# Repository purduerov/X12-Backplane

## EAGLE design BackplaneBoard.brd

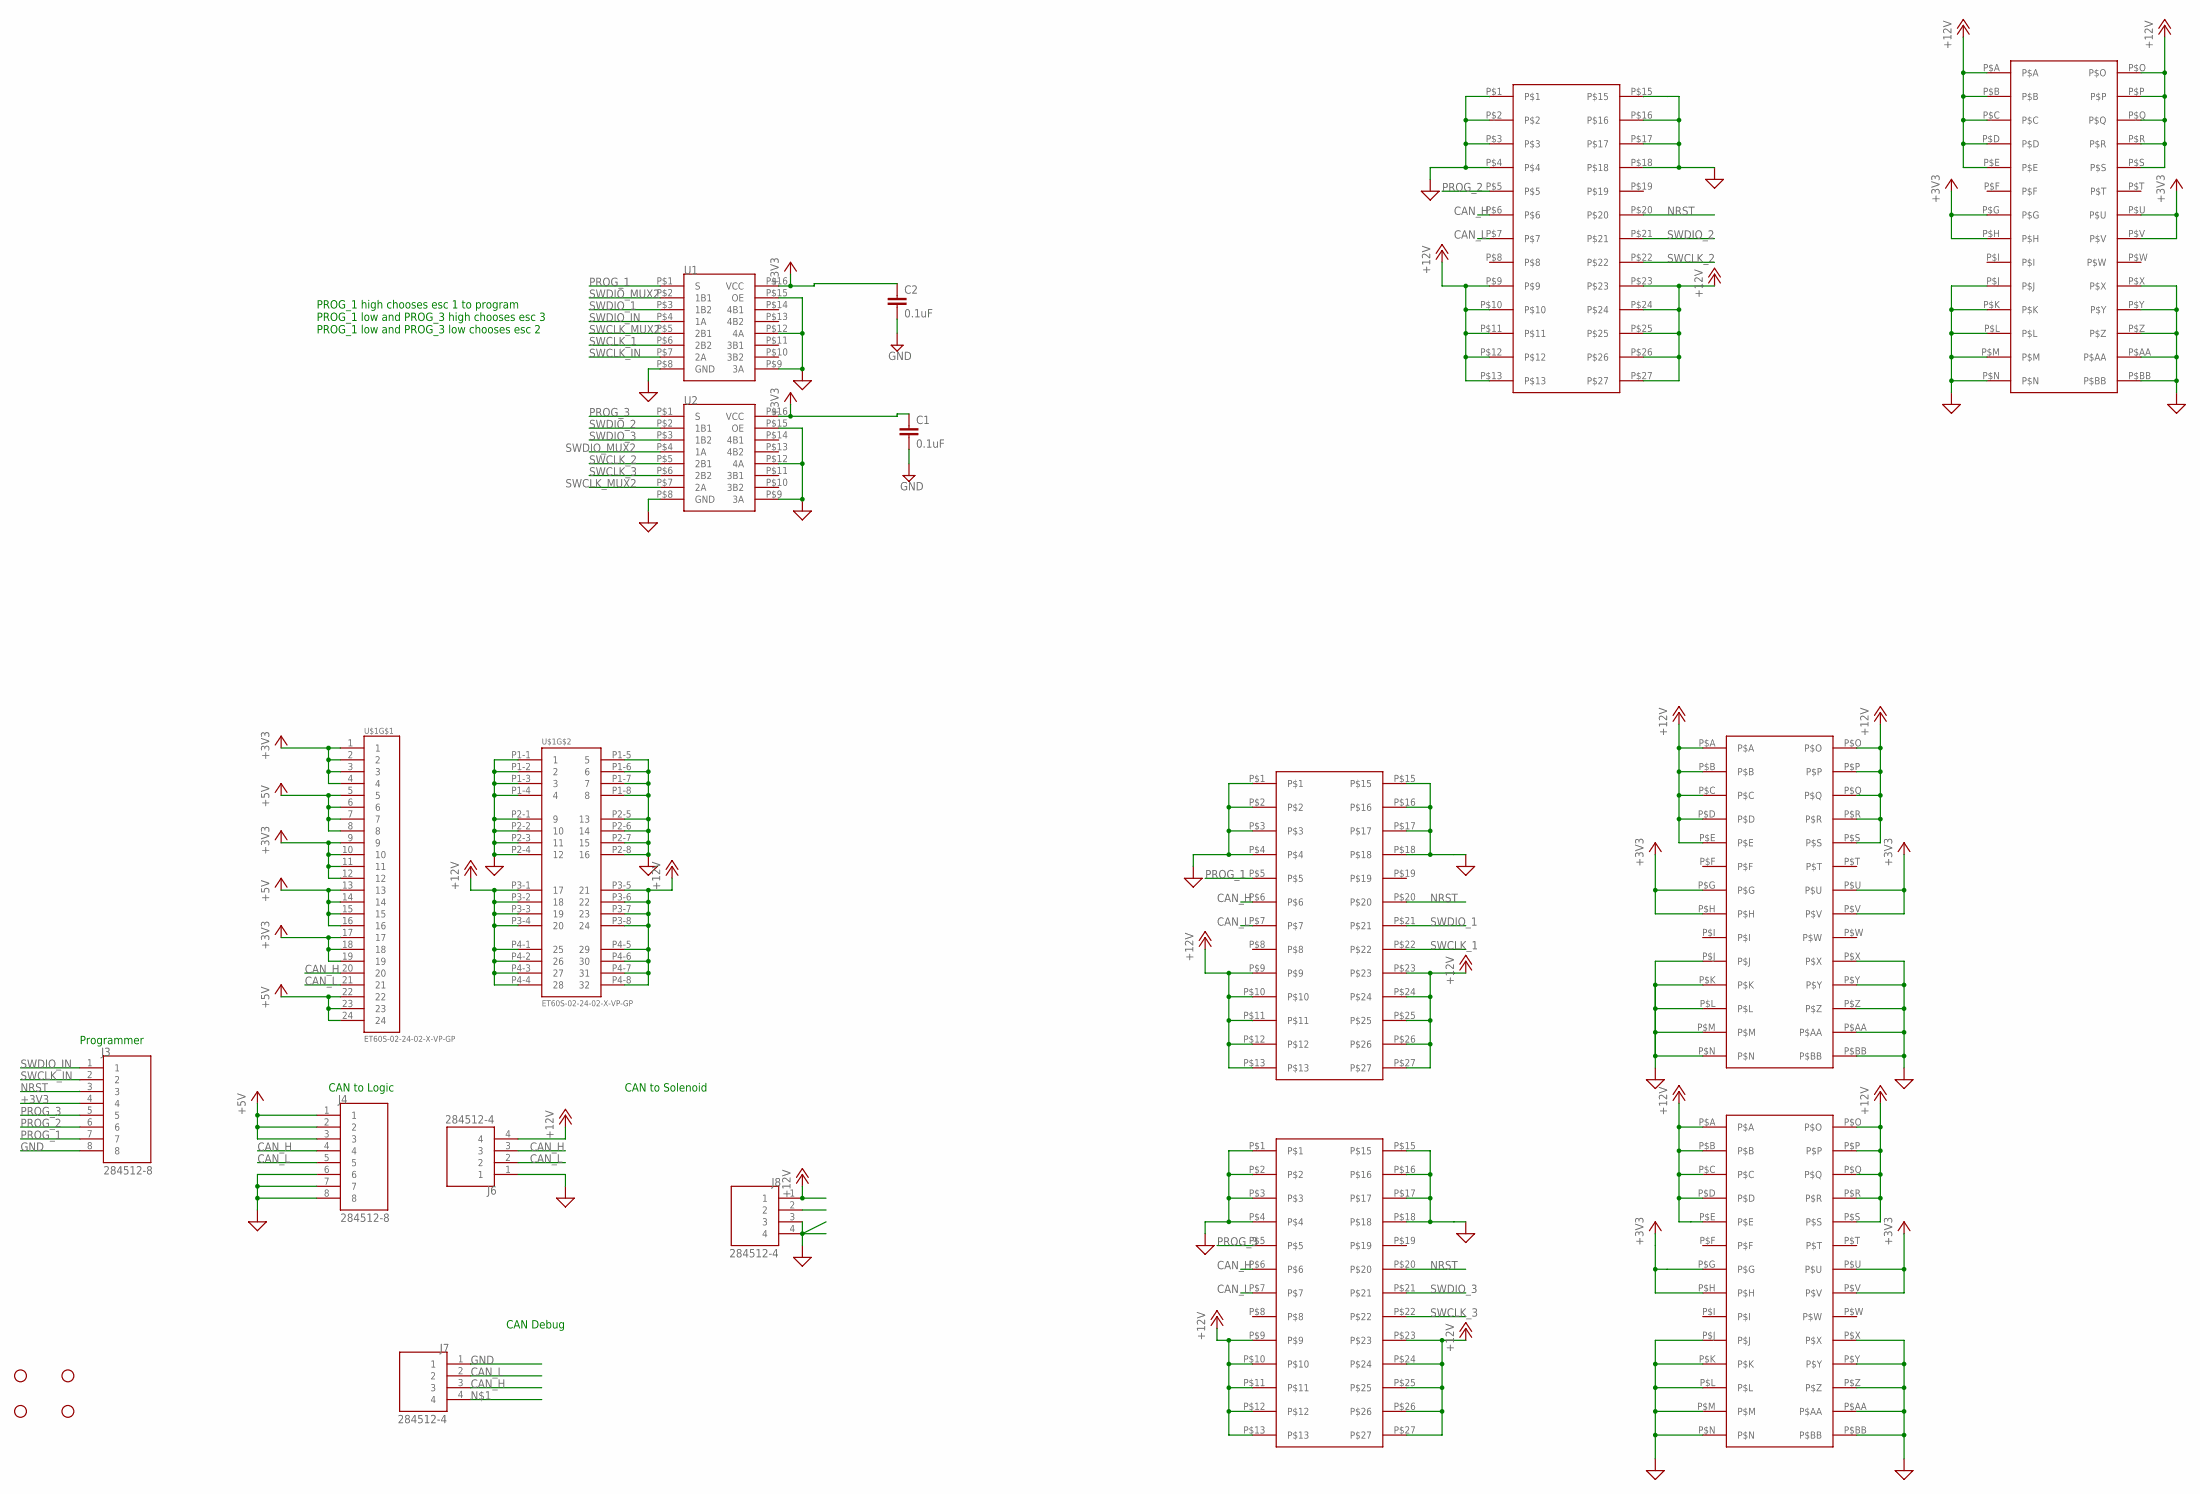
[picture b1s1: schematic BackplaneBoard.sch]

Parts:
C1, C2: 0.1uF; 0603
H1, H2, H3, H4: STAND-OFF
J3, J4: 284512-8; TE_284512-8
J6, J7, J8: 284512-4; TE_284512-4
U1, U2: SN74CBTLV3257PWR
U$1: ET60S-02-24-02-X-VP-GP
U$2, U$3, U$4: ESC2BACKPLANE; ESC2BACKPLANE_WHOLE

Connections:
+3V3: C1.1, C2.1, J3.4, U1.P$16 (VCC), U2.P$16 (VCC), U$1.1, U$1.2, U$1.3, U$1.4, U$1.9, U$1.10, U$1.11, U$1.12, U$1.17, U$1.18, U$1.19, U$2.P$G, U$2.P$H, U$2.P$U, U$2.P$V, U$3.P$G, U$3.P$H, U$3.P$U, U$3.P$V, U$4.P$G, U$4.P$H, U$4.P$U, U$4.P$V
+5V: J4.1, J4.2, J4.3, U$1.5, U$1.6, U$1.7, U$1.8, U$1.13, U$1.14, U$1.15, U$1.16, U$1.22, U$1.23, U$1.24
+12V: J6.4, J8.1, J8.2, U$1.P3-1 (17), U$1.P3-2 (18), U$1.P3-3 (19), U$1.P3-4 (20), U$1.P3-5 (21), U$1.P3-6 (22), U$1.P3-7 (23), U$1.P3-8 (24), U$1.P4-1 (25), U$1.P4-2 (26), U$1.P4-3 (27), U$1.P4-4 (28), U$1.P4-5 (29), U$1.P4-6 (30), U$1.P4-7 (31), U$1.P4-8 (32), U$2.P$9, U$2.P$10, U$2.P$11, U$2.P$12, U$2.P$13, U$2.P$23, U$2.P$24, U$2.P$25, U$2.P$26, U$2.P$27, U$2.P$A, U$2.P$B, U$2.P$C, U$2.P$D, U$2.P$E, U$2.P$O, U$2.P$P, U$2.P$Q, U$2.P$R, U$2.P$S, U$3.P$9, U$3.P$10, U$3.P$11, U$3.P$12, U$3.P$13, U$3.P$23, U$3.P$24, U$3.P$25, U$3.P$26, U$3.P$27, U$3.P$A, U$3.P$B, U$3.P$C, U$3.P$D, U$3.P$E, U$3.P$O, U$3.P$P, U$3.P$Q, U$3.P$R, U$3.P$S, U$4.P$9, U$4.P$10, U$4.P$11, U$4.P$12, U$4.P$13, U$4.P$23, U$4.P$24, U$4.P$25, U$4.P$26, U$4.P$27, U$4.P$A, U$4.P$B, U$4.P$C, U$4.P$D, U$4.P$E, U$4.P$O, U$4.P$P, U$4.P$Q, U$4.P$R, U$4.P$S
CAN_H: J4.4, J6.3, J7.3, U$1.20, U$2.P$6, U$3.P$6, U$4.P$6
CAN_L: J4.5, J6.2, J7.2, U$1.21, U$2.P$7, U$3.P$7, U$4.P$7
GND: C1.2, C2.2, J3.8, J4.6, J4.7, J4.8, J6.1, J7.1, J8.3, J8.4, U1.P$8 (GND), U1.P$9 (3A), U1.P$12 (4A), U1.P$15 (OE), U2.P$8 (GND), U2.P$9 (3A), U2.P$12 (4A), U2.P$15 (OE), U$1.P1-1 (1), U$1.P1-2 (2), U$1.P1-3 (3), U$1.P1-4 (4), U$1.P1-5 (5), U$1.P1-6 (6), U$1.P1-7 (7), U$1.P1-8 (8), U$1.P2-1 (9), U$1.P2-2 (10), U$1.P2-3 (11), U$1.P2-4 (12), U$1.P2-5 (13), U$1.P2-6 (14), U$1.P2-7 (15), U$1.P2-8 (16), U$2.P$1, U$2.P$2, U$2.P$3, U$2.P$4, U$2.P$15, U$2.P$16, U$2.P$17, U$2.P$18, U$2.P$AA, U$2.P$BB, U$2.P$J, U$2.P$K, U$2.P$L, U$2.P$M, U$2.P$N, U$2.P$X, U$2.P$Y, U$2.P$Z, U$3.P$1, U$3.P$2, U$3.P$3, U$3.P$4, U$3.P$15, U$3.P$16, U$3.P$17, U$3.P$18, U$3.P$AA, U$3.P$BB, U$3.P$J, U$3.P$K, U$3.P$L, U$3.P$M, U$3.P$N, U$3.P$X, U$3.P$Y, U$3.P$Z, U$4.P$1, U$4.P$2, U$4.P$3, U$4.P$4, U$4.P$15, U$4.P$16, U$4.P$17, U$4.P$18, U$4.P$AA, U$4.P$BB, U$4.P$J, U$4.P$K, U$4.P$L, U$4.P$M, U$4.P$N, U$4.P$X, U$4.P$Y, U$4.P$Z
NRST: J3.3, U$2.P$20, U$3.P$20, U$4.P$20
PROG_1: J3.7, U1.P$1 (S), U$2.P$5
PROG_2: J3.6, U$3.P$5
PROG_3: J3.5, U2.P$1 (S), U$4.P$5
SWCLK_1: U1.P$6 (2B2), U$2.P$22
SWCLK_2: U2.P$5 (2B1), U$3.P$22
SWCLK_3: U2.P$6 (2B2), U$4.P$22
SWCLK_IN: J3.2, U1.P$7 (2A)
SWCLK_MUX2: U1.P$5 (2B1), U2.P$7 (2A)
SWDIO_1: U1.P$3 (1B2), U$2.P$21
SWDIO_2: U2.P$2 (1B1), U$3.P$21
SWDIO_3: U2.P$3 (1B2), U$4.P$21
SWDIO_IN: J3.1, U1.P$4 (1A)
SWDIO_MUX2: U1.P$2 (1B1), U2.P$4 (1A)

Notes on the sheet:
CAN to Logic
CAN to Solenoid
Programmer
PROG_1 high chooses esc 1 to program PROG_1 low and PROG_3 high chooses esc 3 PROG_1 low and PROG_3 low chooses esc 2
CAN Debug

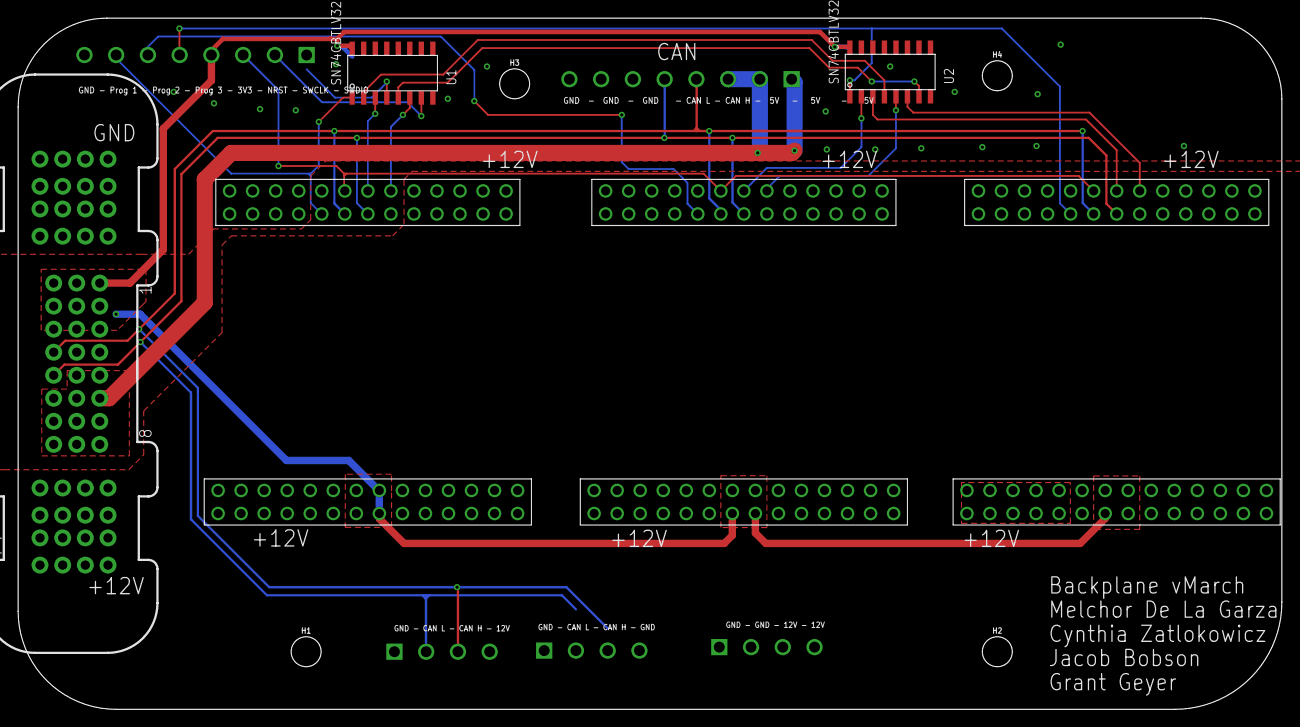
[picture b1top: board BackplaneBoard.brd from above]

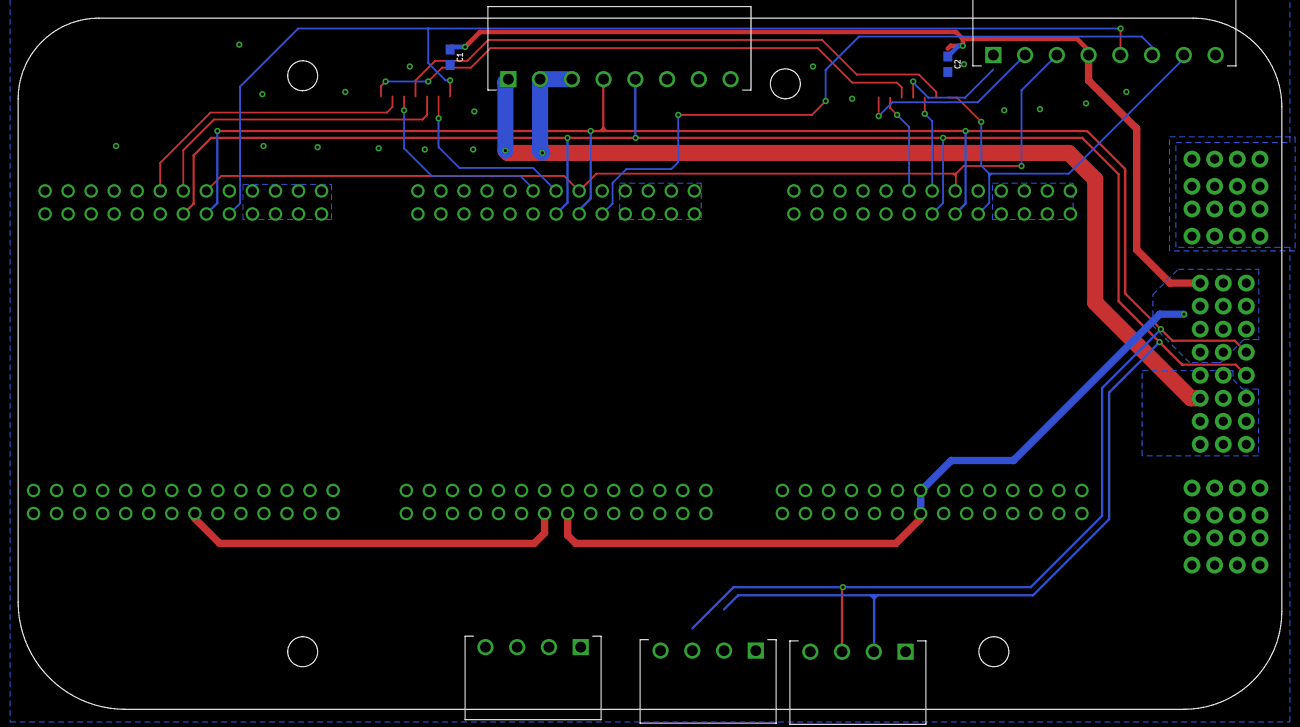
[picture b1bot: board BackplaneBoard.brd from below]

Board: 2 copper layers, 139.3 x 76.2 mm, 17 parts (7 on the bottom side), 20 nets.

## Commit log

2019-09-21 Send it off
2019-10-02 test
2019-11-03 Added right connectors to board
    added right connectors and put board size in, Melchor is slacking
2019-11-04 updated connectors
2019-11-04 added connectors
2019-11-05 updated connectors to jacobs liking
2019-11-05 moved some connectors
2019-11-05 added holes for standoffs
2019-11-07 Netted and labeled pins
2019-11-08 Added polygons to each signal coming from the ESC connecot pins to see placement and corrected a mistake on netting pins
2019-11-09 Added more connections to the pins
    something something did something
2019-11-13 Version1 of the backplane board
2019-11-13 Made Some adjustments
2019-11-15 V2 of Backplane
2019-11-15 fixeey
2019-11-18 Version #3
2019-11-21 Version 4
2019-12-16 edited GND plane
2019-12-16 Small routing changes
2019-12-19 Final Board
2019-12-19 put on cat
2020-01-28 Version 2
2020-02-01 version 3
2020-02-04 New V3
2020-02-09 Backplane V3
2020-02-09 Grants return current fixes
2020-02-13 added connector
2020-02-13 Silk Screen
2020-02-25 gitignore and removed backup files
2020-03-06 consistent
2020-03-07 workable revised state. need new connectors and programming muxing routing
2020-03-09 finished backplane mux
2020-03-10 few minor improvements to the mux
2020-03-13 added new te connectors
2020-03-13 added DXF
2020-03-15 Grants final checks
2020-03-16 fixed connector clearance
2020-03-16 cam files
2020-03-16 updated DXF for connector location
2020-03-19 trace corners
2020-03-26 tried net classes
2020-09-04 all connector cad
2020-09-09 partial connector cad for going to the ESCs

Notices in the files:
parts and their libraries:
SparkFun-Hardware: Licensing: Creative Commons ShareAlike 4.0 International - https://creativecommons.org/licenses/by-sa/4.0
